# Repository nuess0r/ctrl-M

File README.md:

# Ctrl M Controller for Model M

This is a replacement controller for the famous IBM Model M keyboard based on the STM32F072 microcontroller. Goal is to get it upstream in QMK.

Work in progress, prototypes are working in Model M from 1989, there is a bug for the version from 1986 and test for other variants are outstanding.

## Hardware

Controller based on a STM32F072 chip and designed with KiCAD.

To make the controller as flexible as possible there are four possible LED and earth cable connectors. Also the PCB can be cut into a smaller variant that fits the later IBM/Lexmark variant.

The four LED connector variants are:

    J8 is a 12 pin connector is mounted for J8 for both LED and keyboard
    J8 is a 8 pin connector and J9 is a 4 pin connector
    J8 is a 8 pin connector and J12 is a 4 pin connector
    J8 is a 8 pin connector and J10 is a 4 pin header

https://github.com/nuess0r/ctrl-M

To fill the gab between the USB connector and the case and also to make it easier to press the bootloader button a small plastic part (button_lever.amf) was designed with FreeCAD that can be 3D printed.

## Software

https://github.com/nuess0r/qmk_firmware/tree/ctrl_m/keyboards/ctrl_m

## Assembly Instructions

https://brain4free.org/wiki/doku.php/elektronik:ctrl_m#assembly_instructions

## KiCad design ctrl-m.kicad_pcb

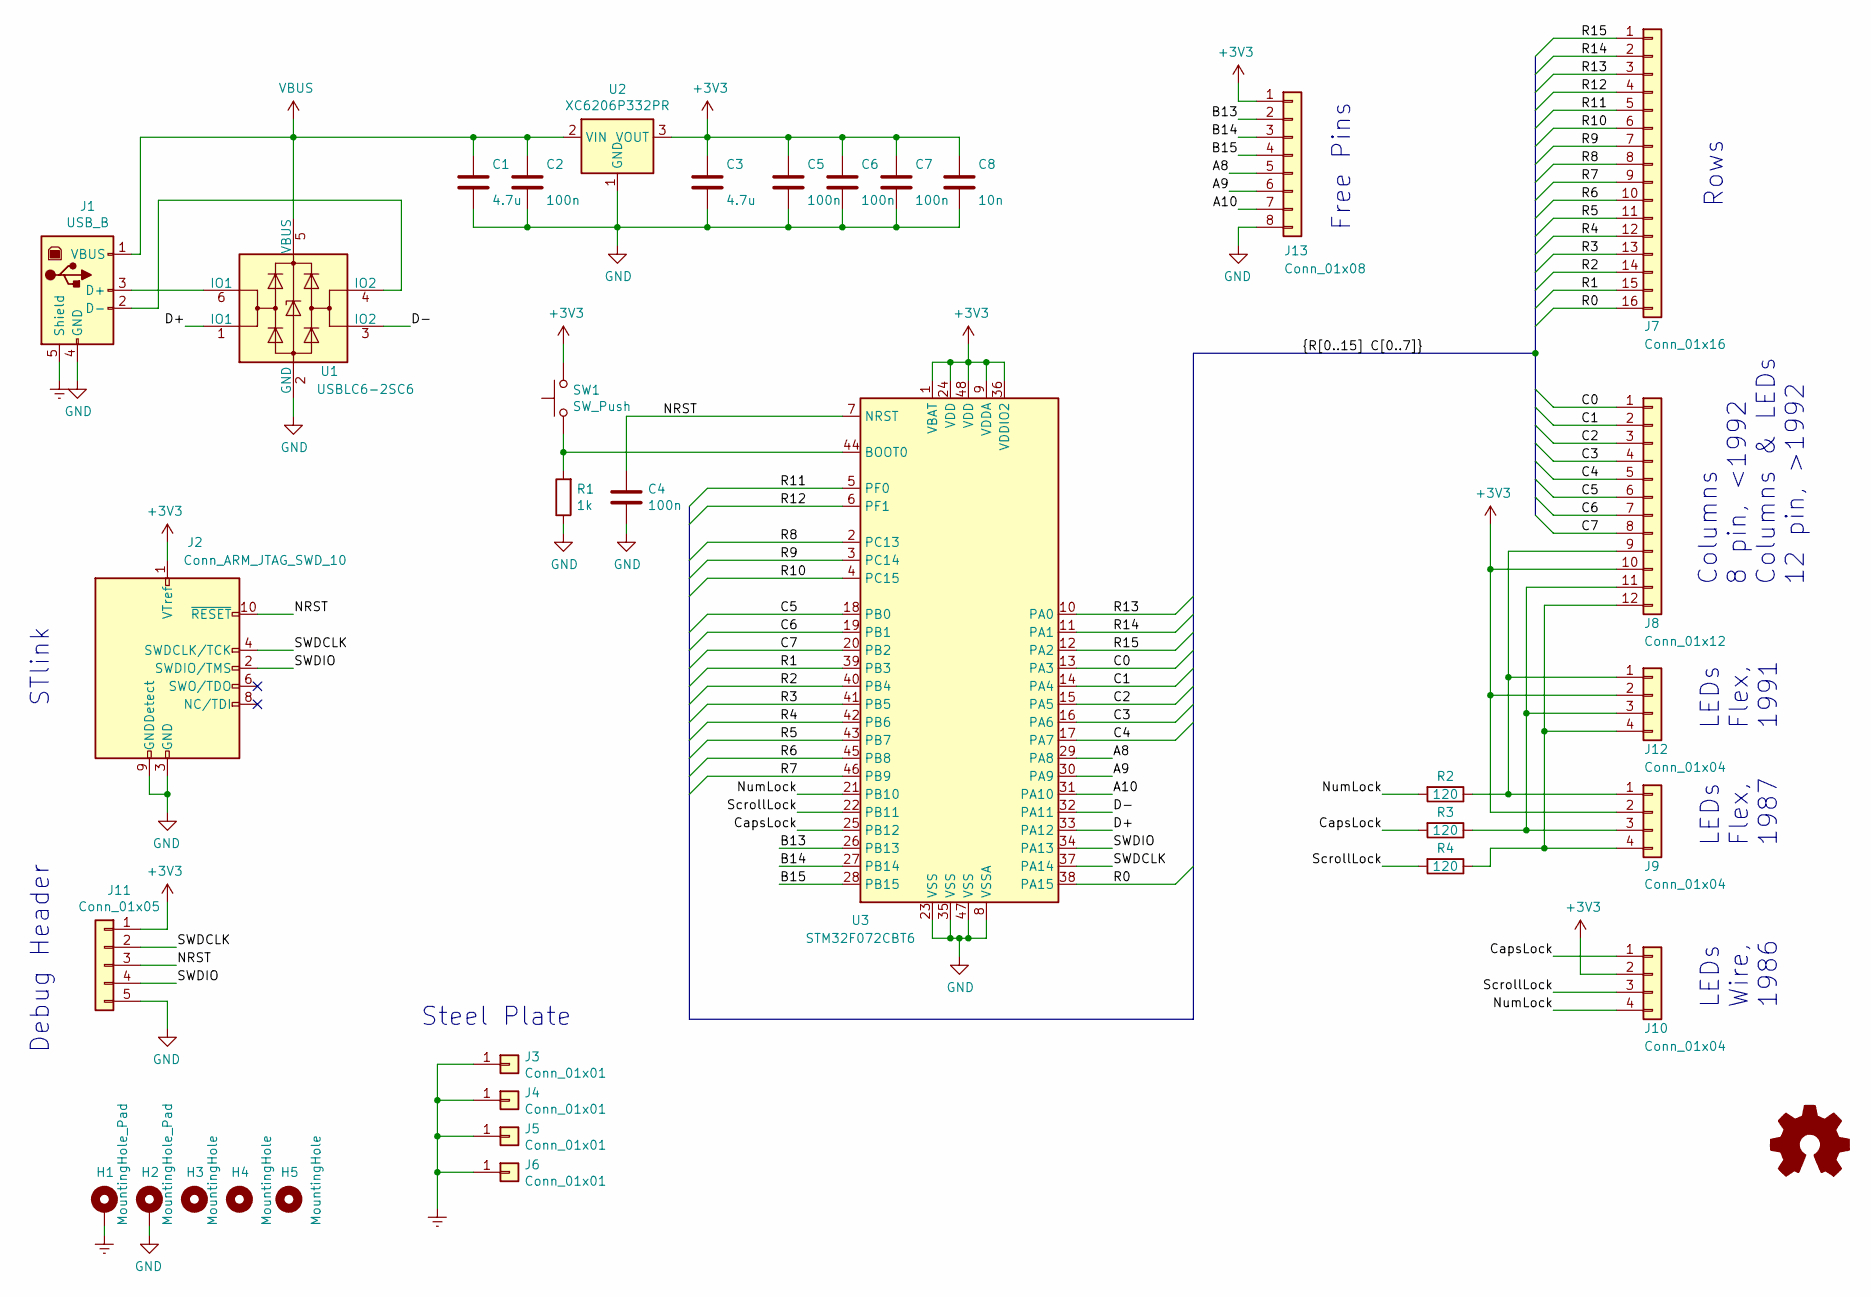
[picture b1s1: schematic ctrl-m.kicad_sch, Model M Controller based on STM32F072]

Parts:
C1, C3: 4.7u; C_0805_2012Metric
C2, C4, C5, C6, C7: 100n; C_0603_1608Metric
C8: 10n; C_0603_1608Metric
H1, H2: MountingHole_Pad; MountingHole_3.2mm_M3_Pad
H3, H4: MountingHole; MountingHole_4mm_Pad
H5: MountingHole; MountingHole_2.1mm
J1: USB_B; USB_B_OST_USB-B1HSxx_Horizontal
J2: Conn_ARM_JTAG_SWD_10; PinHeader_2x05_P1.27mm_Vertical
J3, J4, J5, J6: Conn_01x01; Blade_6.3mm_Horizontal
J7: Conn_01x16; TE_6-520315-6_1x16_P2.54mm_Vertical
J8: Conn_01x12; TE_6-520315-2_1x12_P2.54mm_Vertical
J9, J12: Conn_01x04; TE_5-520315-4_1x04_P2.54mm_Vertical
J10: Conn_01x04; PinHeader_1x04_P2.54mm_Horizontal
J11: Conn_01x05; PinHeader_1x05_P2.54mm_Vertical
J13: Conn_01x08; PinHeader_1x08_P2.54mm_Vertical
R1: 1k; R_0603_1608Metric
R2, R3, R4: 120; R_0603_1608Metric
SW1: SW_Push; SW_SPST_UK_B0205-G4.3-B-250
U1: USBLC6-2SC6; SOT-23-6
U2: XC6206P332PR; SOT-89-3
U3: STM32F072CBT6; LQFP-48_7x7mm_P0.5mm

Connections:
+3V3: C3.1, C5.1, C6.1, C7.1, C8.1, J2.1 (VTref), J8.10, J9.2, J10.2, J11.1, J12.2, J13.1, SW1.2, U2.3 (VOUT), U3.1 (VBAT), U3.9 (VDDA), U3.24 (VDD), U3.36 (VDDIO2), U3.48 (VDD)
/A8: J13.5, U3.29 (PA8)
/A9: J13.6, U3.30 (PA9)
/A10: J13.7, U3.31 (PA10)
/B13: J13.2, U3.26 (PB13)
/B14: J13.3, U3.27 (PB14)
/B15: J13.4, U3.28 (PB15)
/C0: J8.1, U3.13 (PA3)
/C1: J8.2, U3.14 (PA4)
/C2: J8.3, U3.15 (PA5)
/C3: J8.4, U3.16 (PA6)
/C4: J8.5, U3.17 (PA7)
/C5: J8.6, U3.18 (PB0)
/C6: J8.7, U3.19 (PB1)
/C7: J8.8, U3.20 (PB2)
/CapsLock: J10.1, R3.2, U3.25 (PB12)
/D+: U1.1 (IO1), U3.33 (PA12)
/D-: U1.3 (IO2), U3.32 (PA11)
/NRST: C4.1, J2.10 (~RESET), J11.3, U3.7 (NRST)
/NumLock: J10.4, R2.2, U3.21 (PB10)
/R0: J7.16, U3.38 (PA15)
/R1: J7.15, U3.39 (PB3)
/R2: J7.14, U3.40 (PB4)
/R3: J7.13, U3.41 (PB5)
/R4: J7.12, U3.42 (PB6)
/R5: J7.11, U3.43 (PB7)
/R6: J7.10, U3.45 (PB8)
/R7: J7.9, U3.46 (PB9)
/R8: J7.8, U3.2 (PC13)
/R9: J7.7, U3.3 (PC14)
/R10: J7.6, U3.4 (PC15)
/R11: J7.5, U3.5 (PF0)
/R12: J7.4, U3.6 (PF1)
/R13: J7.3, U3.10 (PA0)
/R14: J7.2, U3.11 (PA1)
/R15: J7.1, U3.12 (PA2)
/SWDCLK: J2.4 (SWDCLK/TCK), J11.2, U3.37 (PA14)
/SWDIO: J2.2 (SWDIO/TMS), J11.4, U3.34 (PA13)
/ScrollLock: J10.3, R4.2, U3.22 (PB11)
Earth: H1.1, J1.5 (Shield), J3.1, J4.1, J5.1, J6.1
GND: C1.2, C2.2, C3.2, C4.2, C5.2, C6.2, C7.2, C8.2, H2.1, J1.4 (GND), J2.3 (GND), J2.5 (GND), J2.9 (GNDDetect), J11.5, J13.8, R1.1, U1.2 (GND), U2.1 (GND), U3.8 (VSSA), U3.23 (VSS), U3.35 (VSS), U3.47 (VSS)
unnamed: J1.3 (D+), U1.6 (IO1)
unnamed: J1.2 (D-), U1.4 (IO2)
unnamed: J8.9, J9.1, J12.1, R2.1
unnamed: J8.11, J9.3, J12.3, R3.1
unnamed: J8.12, J9.4, J12.4, R4.1
unnamed: R1.2, SW1.1, U3.44 (BOOT0)
VBUS: C1.1, C2.1, J1.1 (VBUS), U1.5 (VBUS), U2.2 (VIN)

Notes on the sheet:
LEDs Flex, 1987
LEDs Flex, 1991
Columns 8 pin, <1992 Columns & LEDs 12 pin, >1992
LEDs Wire, 1986
Debug Header
Steel Plate
Rows
Free Pins
STlink

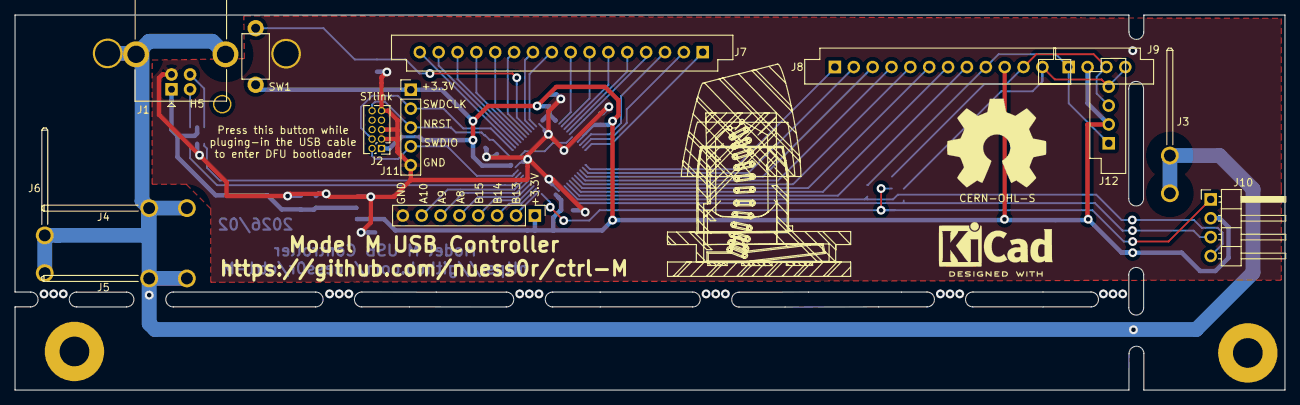
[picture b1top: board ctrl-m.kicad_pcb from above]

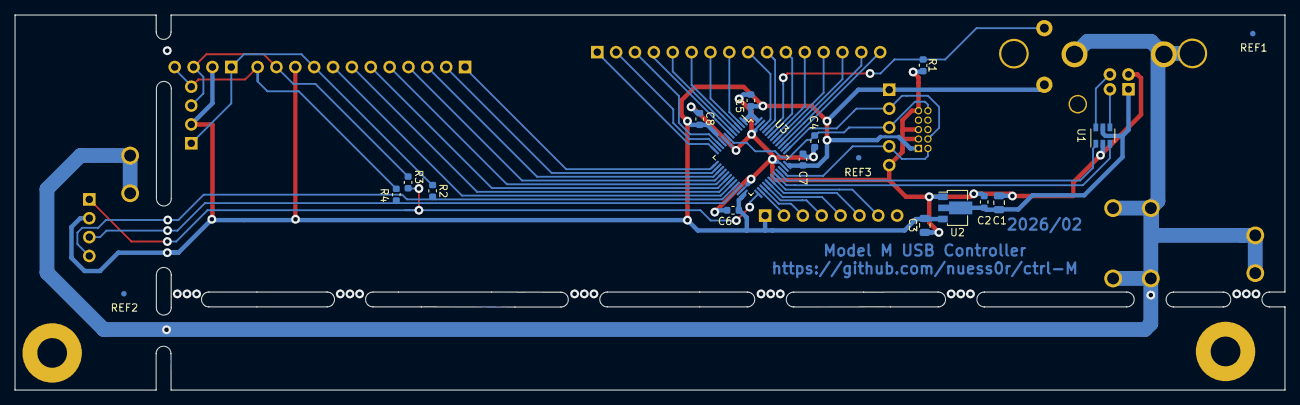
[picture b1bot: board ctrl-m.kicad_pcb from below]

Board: 2 copper layers, 171.0 x 50.5 mm, 37 parts (18 on the bottom side), 48 nets.

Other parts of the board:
REF1, REF2, REF3: Fiducial_0.75mm_Mask1.5mm

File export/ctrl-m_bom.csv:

Comment,Designator,Footprint,LCSC
"4.7u","C1,C3","Capacitor_SMD:C_0805_2012Metric",""
"100n","C2,C4,C5,C6,C7","Capacitor_SMD:C_0603_1608Metric",""
"10n","C8","Capacitor_SMD:C_0603_1608Metric",""
"MountingHole_Pad","H1,H2","MountingHole:MountingHole_3.2mm_M3_Pad",""
"MountingHole","H3,H4","MountingHole:MountingHole_4mm_Pad",""
"USB_B","J1","Connector_USB:USB_B_OST_USB-B1HSxx_Horizontal",""
"Conn_01x04","J10","Connector_PinHeader_2.54mm:PinHeader_1x04_P2.54mm_Horizontal",""
"Conn_01x05","J11","Connector_PinHeader_2.54mm:PinHeader_1x05_P2.54mm_Vertical",""
"Conn_01x04","J9,J12","Connector_FPC_2.54mm:TE_5-520315-4_1x04_P2.54mm_Vertical",""
"Conn_ARM_JTAG_SWD_10","J2","Connector_PinHeader_1.27mm:PinHeader_2x05_P1.27mm_Vertical",""
"Conn_01x01","J3,J4,J5,J6","Connector_Blade:Blade_6.3mm_Horizontal",""
"Conn_01x16","J7","Connector_FPC_2.54mm:TE_6-520315-6_1x16_P2.54mm_Vertical",""
"Conn_01x12","J8","Connector_FPC_2.54mm:TE_6-520315-2_1x12_P2.54mm_Vertical",""
"1k","R1","Resistor_SMD:R_0603_1608Metric",""
"120","R2,R3,R4","Resistor_SMD:R_0603_1608Metric",""
"SW_Push","SW1","Button_Switch_THT_narrow:SW_SPST_UK_B0205-G4.3-B-250",""
"USBLC6-2SC6","U1","Package_TO_SOT_SMD:SOT-23-6",""
"XC6206P332PR","U2","Package_TO_SOT_SMD:SOT-89-3",""
"STM32F072CBT6","U3","Package_QFP:LQFP-48_7x7mm_P0.5mm",""

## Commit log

2021-03-24 Initial release
    Ready to order prototypes. Testing is outstanding.
2021-03-27 Changed LDO type to one that is stable with ceramic capacitors
    LD1117 is unstable with this low output capacitance and in general with
    ceramic capacitors.
    Also it needs 10 mA minimum load which is not guaranteed when all LEDs are off.
    Replaced with a much more recent chip the XC6206P332PR
2021-07-22 Optimize for production
    Applied design rules of prototype manufacturer
    Fixed DRC errors
2023-01-19 Add FreeCAD model of a spacer and lever to actuate the button
    The USB connector is less tall than the original connector.
    With this 3D printed part this gap can be filled and also
    a lever is added to push the button.
2023-03-05 Making the button lever more robust
2023-05-31 Fix pinning of J10 in schematic
    And upgrade to KiCAD 6
2023-05-31 Update PCB to wider holes for the plastic pegs and J10 wiring fix
    This solves issue #3 and #4
2023-05-31 Add STEP file for better compatibility with online shops
2023-07-23 Move button_lever to correct position (change on PCB and 3D model)
2023-09-23 Exported button_lever.amf was empty
2024-08-03 Modified button lever to be easier to print
2026-02-12 Enhancement: have unused pins ending on a pad #8
    Also migrated to KiCAD 9

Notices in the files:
ctrl-m.kicad_pcb:
This source describes Open Hardware and is licensed under the CERN-OHL-S v2\
under the terms of the CERN-OHL-S v2 (https:/cern.ch/cern-ohl).\
Copyright Christoph Zimmermann 2021.
CERN-OHL-S
